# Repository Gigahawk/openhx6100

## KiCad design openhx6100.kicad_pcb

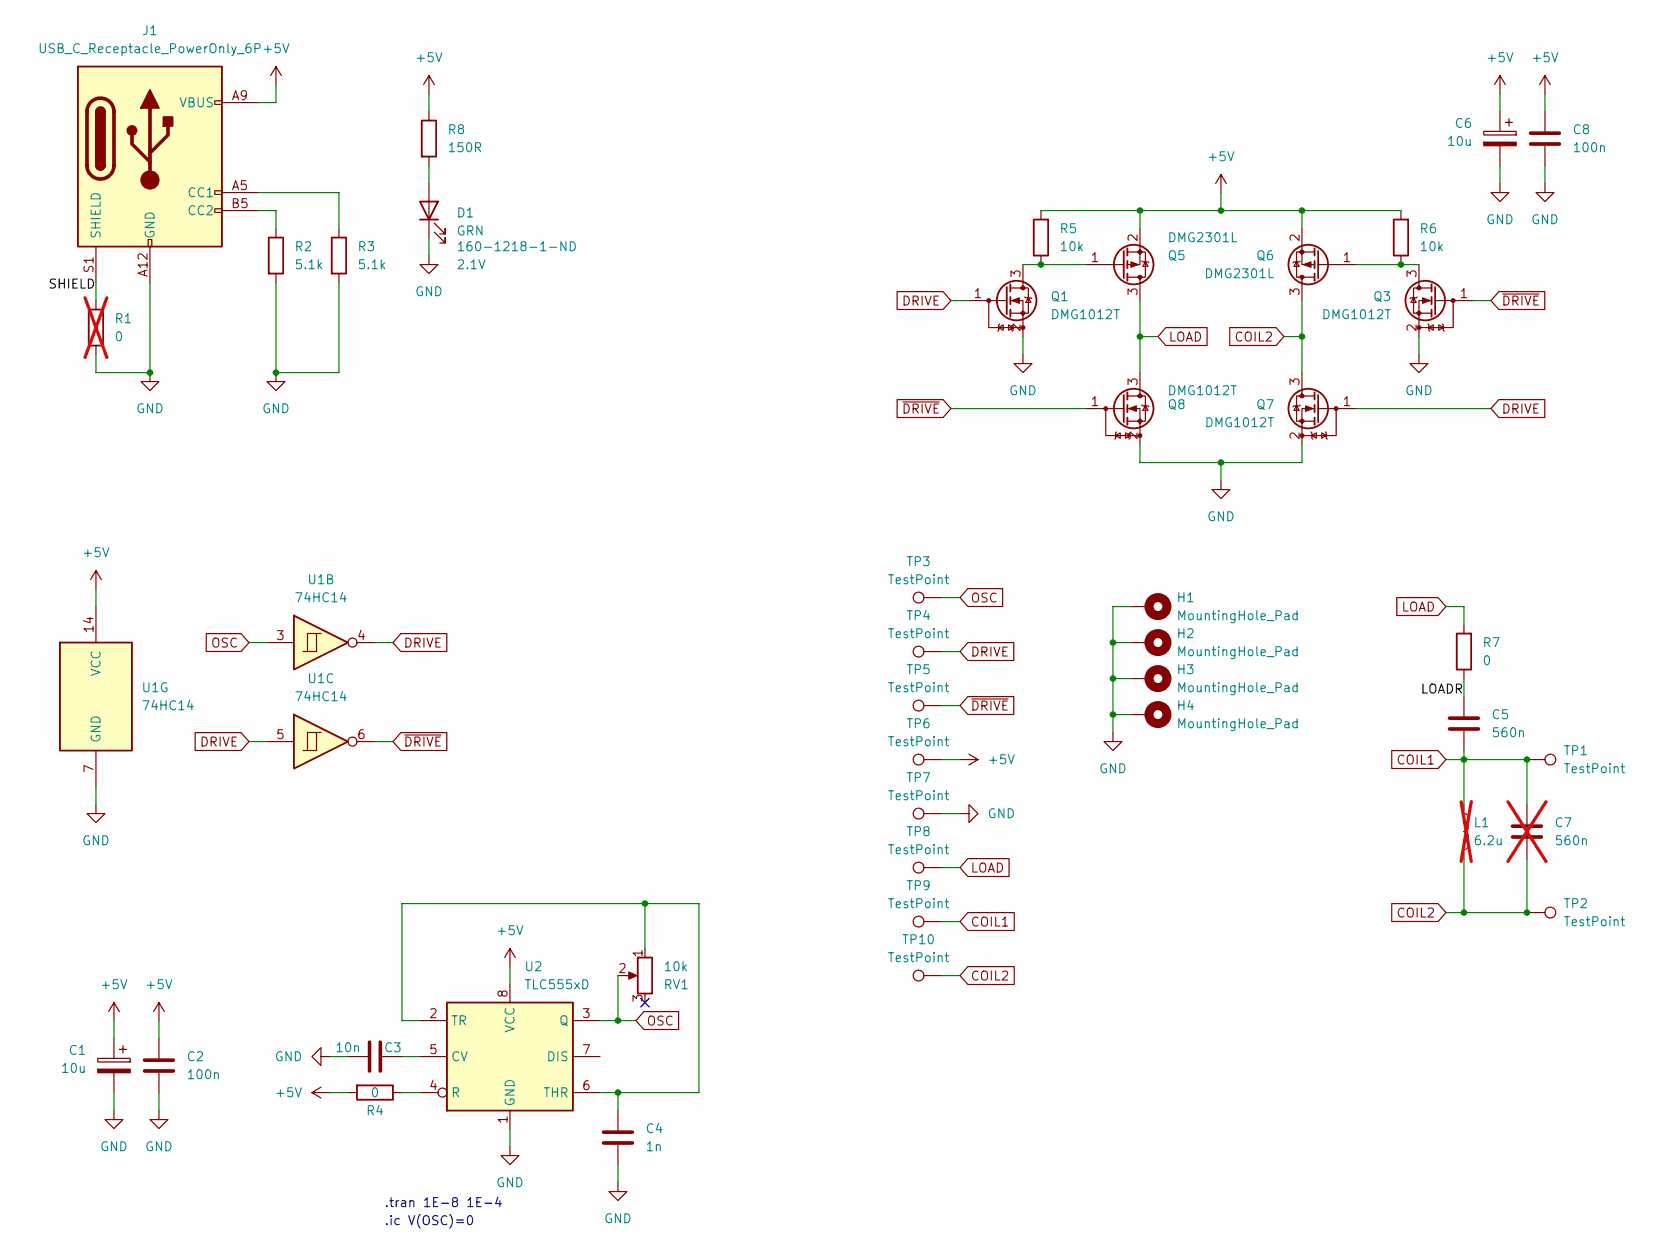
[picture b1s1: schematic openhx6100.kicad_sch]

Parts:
C1, C6: 10u; CP_Elec_4x5.4; Digikey 493-2173-1-ND
C2, C8: 100n; C_0805_2012Metric_Pad1.18x1.45mm_HandSolder; Digikey 478-KGM21NR71H104KMCT-ND
C3: 10n; C_0805_2012Metric_Pad1.18x1.45mm_HandSolder; Digikey CC0805KRX7R9BB103
C4: 1n; C_0805_2012Metric_Pad1.18x1.45mm_HandSolder; Digikey 399-C0805C102K5RAC7800CT-ND
C5: 560n; C_1206_3216Metric_Pad1.33x1.80mm_HandSolder; Digikey 399-C0805C564K5RAC7800CT-ND
C7: 560n; C_1206_3216Metric_Pad1.33x1.80mm_HandSolder; Digikey 399-C0805C564K5RAC7800CT-ND; not fitted
D1: GRN; LED_0805_2012Metric_Pad1.15x1.40mm_HandSolder; Digikey 160-1218-1-ND
H1, H2, H3, H4: MountingHole_Pad; MountingHole_2.2mm_M2_DIN965_Pad
J1: USB_C_Receptacle_PowerOnly_6P; UJC-HP-3-SMT-TR; Digikey 2223-UJC-HP-3-SMT-CT-ND
L1: 6.2u; Digikey 445-174580-ND; not fitted
Q1, Q3, Q7, Q8: DMG1012T; SOT-523; Digikey DMG1012T-7DICT-ND
Q5, Q6: DMG2301L; SOT-23; Digikey DMG2301L-7DICT-ND
R1: 0; R_0805_2012Metric_Pad1.20x1.40mm_HandSolder; Digikey RMCF0805ZT0R00CT-ND; not fitted
R2, R3: 5.1k; R_0805_2012Metric_Pad1.20x1.40mm_HandSolder; Digikey 311-5.1KARCT-ND
R4, R7: 0; R_0805_2012Metric_Pad1.20x1.40mm_HandSolder; Digikey RMCF0805ZT0R00CT-ND
R5, R6: 10k; R_0805_2012Metric_Pad1.20x1.40mm_HandSolder; Digikey 311-10KARCT-ND
R8: 150R; R_0805_2012Metric_Pad1.20x1.40mm_HandSolder; Digikey 311-150HRCT-ND
RV1: 10k; Potentiometer_Bourns_TC33X_Vertical; Digikey TC33X-103ECT-ND
TP1, TP2: TestPoint; TestPoint_Pad_4.0x4.0mm
TP3, TP4, TP5, TP6, TP7, TP8, TP9, TP10: TestPoint; TestPoint_Keystone_5000-5004_Miniature; Digikey 36-5000-ND
U1: 74HC14; TSSOP-14_4.4x5mm_P0.65mm; Digikey 296-8234-1-ND
U2: TLC555xD; SOIC-8_3.9x4.9mm_P1.27mm; Digikey 296-1336-1-ND

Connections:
+5V: C1.1, C2.1, C6.1, C8.1, J1.A9 (VBUS), J1.B9 (VBUS), Q5.2 (S), Q6.2 (S), R4.2, R5.2, R6.2, R8.1, TP6.1, U1.14 (VCC), U2.8 (VCC)
/LOADR: C5.1, R7.1
/SHIELD: J1.S1 (SHIELD), R1.1
COIL1: C5.2, C7.1, L1.1, TP1.1, TP9.1
COIL2: C7.2, L1.2, Q6.3 (D), Q7.3 (D), TP2.1, TP10.1
DRIVE: Q1.1 (G), Q7.1 (G), TP4.1, U1.4, U1.5
GND: C1.2, C2.2, C3.1, C4.2, C6.2, C8.2, D1.1 (K), H1.1, H2.1, H3.1, H4.1, J1.A12 (GND), J1.B12 (GND), Q1.2 (S), Q3.2 (S), Q7.2 (S), Q8.2 (S), R1.2, R2.2, R3.2, TP7.1, U1.7 (GND), U2.1 (GND)
LOAD: Q5.3 (D), Q8.3 (D), R7.2, TP8.1
unnamed: D1.2 (A), R8.2
unnamed: J1.A5 (CC1), R3.1
unnamed: J1.B5 (CC2), R2.1
unnamed: Q1.3 (D), Q5.1 (G), R5.1
unnamed: Q3.3 (D), Q6.1 (G), R6.1
unnamed: C3.2, U2.5 (CV)
unnamed: R4.1, U2.4 (R)
unnamed: C4.1, RV1.1, U2.2 (TR), U2.6 (THR)
OSC: RV1.2, TP3.1, U1.3, U2.3 (Q)
~DRIVE: Q3.1 (G), Q8.1 (G), TP5.1, U1.6

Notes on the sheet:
.tran 1E-8 1E-4
.ic V(OSC)=0

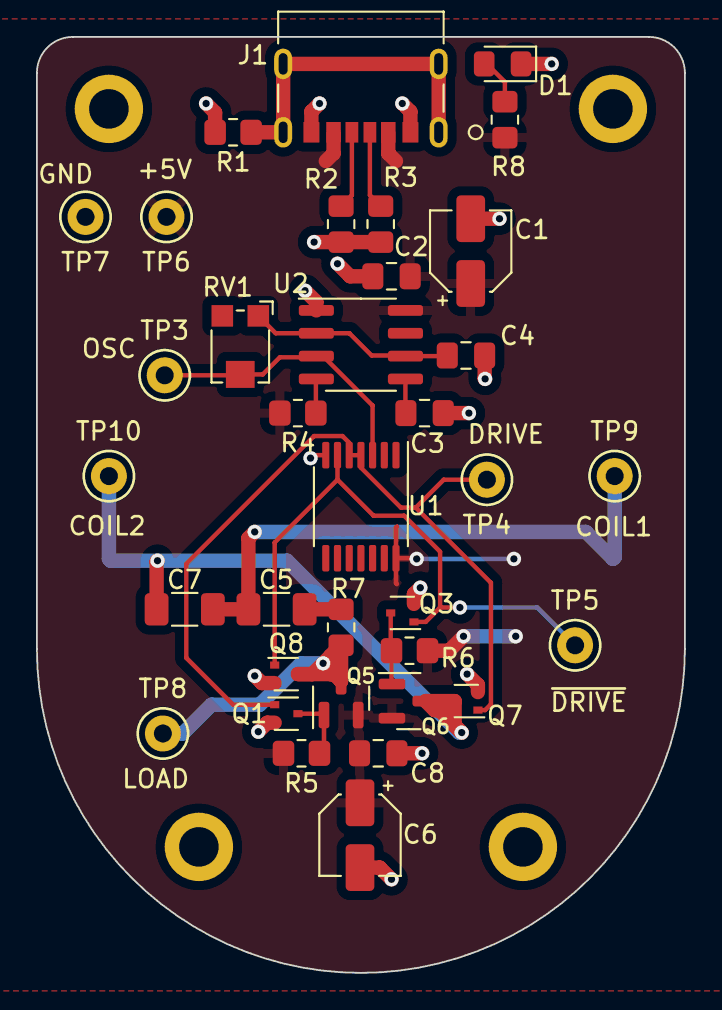
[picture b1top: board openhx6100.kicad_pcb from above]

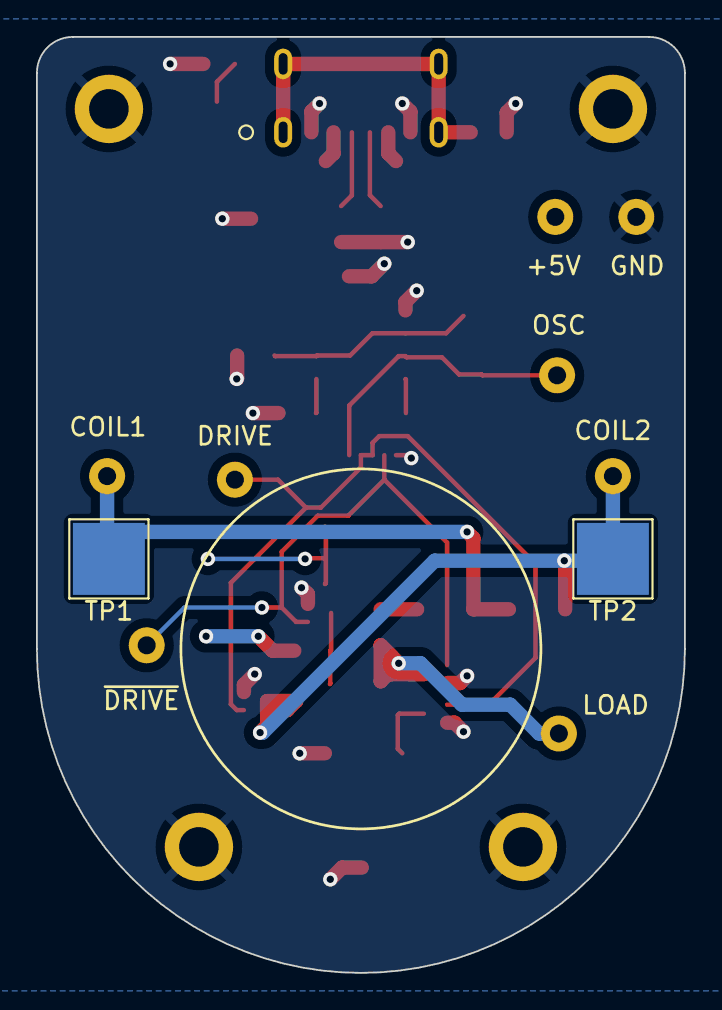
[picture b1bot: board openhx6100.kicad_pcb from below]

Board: 2 copper layers, 36.0 x 52.0 mm, 41 parts (2 on the bottom side), 18 nets.

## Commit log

2023-06-22 sim: implement oscillator
    - Simulation only looks good when using NE555 model, may need redesign
    for TLC555
2023-06-23 sim: switch to discrete bjt h-bridge
2023-06-27 sim: switch to discrete mosfet h-bridge
2023-09-25 layout: create pcb layout
2023-09-26 layout: finish layout
2023-09-26 ci: enable ci
2023-09-26 cleanup: remove old bom
2023-09-26 bom: fill out bom
2023-09-26 feature: add revision info
